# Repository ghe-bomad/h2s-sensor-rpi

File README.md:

# H2S sensor board for Raspberry Pi

An open hardware board that measures hydrogen sulphide (H2S) from 0 to 1000 ppm, with a Python package and command-line tool that read it on a Raspberry Pi over I2C. It was built for biogas monitoring and works anywhere a Raspberry Pi needs a calibrated H2S reading.

## Features

- **Sensor:** Euro-Gas 4-H2S-1000 electrochemical cell (Honeywell CLE-0113-400), 0 to 1000 ppm, overload 2000 ppm.
- **Analog front end:** TI LMP91002 potentiostat with an external 2.5 V reference (ADR3425), so the zero point does not move with the supply.
- **ADC:** 16-bit ADS1115, about 0.2 ppm per step.
- **Temperature compensation:** an NTC thermistor sits under the cell and feeds the datasheet's temperature curves, or your own.
- **Wiring:** four wires to the Pi (5 V, GND, SDA, SCL) on a screw terminal.
- **Software:** a Python package (`h2s-reader`) with calibration files, CSV logging and averaging. Its tests run without hardware.

| | |
|---|---|
| Board size | 59.7 × 31.9 mm, four M3 holes (51.5 × 23.4 mm) |
| Supply | 5 V from the Raspberry Pi, 3.3 V regulated on board |
| I2C addresses | 0x48 (LMP91002), 0x49 (ADS1115) |
| Spare input | AIN3 of the ADS1115 on a 3-pin header (GND, 3.3 V, AIN3) |

## Quick start

1. **Build or order the board** with the files in [`hardware/`](hardware/README.md), and plug the 4-H2S-1000 cell into its sockets.
2. **Wire it to the Pi:**

   | Board (CN1) | Raspberry Pi header |
   |---|---|
   | 5V | pin 2 (5 V) |
   | GND | pin 6 (GND) |
   | SDA | pin 3 (GPIO 2, SDA) |
   | SCL | pin 5 (GPIO 3, SCL) |

3. **Enable I2C and install the package:**

   ```bash
   sudo raspi-config nonint do_i2c 0
   sudo apt install -y i2c-tools python3-venv
   i2cdetect -y 1                       # shows 48 and 49
   python3 -m venv ~/h2s && ~/h2s/bin/pip install "git+https://github.com/ghe-bomad/h2s-sensor-rpi#subdirectory=software"
   ~/h2s/bin/h2s-reader --selftest
   ~/h2s/bin/h2s-reader --stream
   ```

4. **Bring the board up** as described in [docs/bring-up.md](docs/bring-up.md).
5. **Calibrate the cell** with certified test gas ([docs/calibration.md](docs/calibration.md)). Until then readings can be up to ±44 % off, because cells differ that much.

## Documentation

| | |
|---|---|
| [hardware/README.md](hardware/README.md) | schematic, bill of materials, ordering, assembly, design checks |
| [software/README.md](software/README.md) | installing, command line, Python API, calibration file, tests |
| [docs/how-it-works.md](docs/how-it-works.md) | signal chain, range and resolution, temperature compensation |
| [docs/bring-up.md](docs/bring-up.md) | first power-up and checks, notes for use in biogas |
| [docs/calibration.md](docs/calibration.md) | zero, span and temperature calibration |
| [CHANGELOG.md](CHANGELOG.md) | changes per version |

## Repository layout

```
hardware/
  kicad/            KiCad 10 project and footprints
  production/       gerbers, BOM and positions for JLCPCB (H2S-RPi-V1)
  datasheets/       cell, LMP91002 and ADS1115 datasheets
  images/           board renders
  schematic.pdf     schematic export
  check.sh          ERC, DRC and exports with kicad-cli
software/
  h2s_reader/       Python package
  tests/            pytest suite (simulated I2C bus)
  calibration.example.toml
docs/               how it works, bring-up, calibration
```

## Status

- **Version:** 1 (H2S-RPi-V1).
- **Board design:** KiCad's ERC and DRC report only reviewed, non-critical items (see [hardware/README.md](hardware/README.md#design-checks)).
- **Software:** tested against a simulated I2C bus.
- **Not yet validated:** the response to certified H2S test gas. Calibration values are still to be measured.

## License

- **Hardware** (`hardware/`): [CERN-OHL-P-2.0](LICENSE-HARDWARE).
- **Software and documentation:** [MIT](LICENSE-SOFTWARE).
- **Datasheets:** belong to their manufacturers. See [LICENSE](LICENSE).

Developed at ETH Zurich, Global Health Engineering.

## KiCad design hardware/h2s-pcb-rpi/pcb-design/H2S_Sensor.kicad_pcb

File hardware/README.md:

# Hardware

KiCad 10 project of the H2S sensor board, version H2S-RPi-V1. The full schematic is in [schematic.pdf](schematic.pdf).

| Top | Bottom |
|---|---|
|  |  |

## Circuit

| Ref | Part | Function |
|---|---|---|
| J5 | Euro-Gas 4-H2S-1000 cell (not in the BOM, order separately) | working (WE), counter (CE) and reference (RE) electrodes |
| U2 | LMP91002SDX | potentiostat: holds RE at the zero bias, converts the WE current to a voltage (7 kΩ internal gain) |
| U3 | ADR3425 | 2.5 V reference for the LMP91002 (`VREF`) |
| U7 | ADS1115IDGS | 16-bit ADC: AIN0 = LMP91002 output, AIN1 = GND, AIN2 = NTC divider, AIN3 = header H5 |
| TH1, R3 | NTC 10 kΩ (B 3950), 10 kΩ | temperature divider: 3.3 V, R3, AIN2, TH1, GND. TH1 sits under the cell |
| U1 | LP5907MFX-3.3 | 3.3 V regulator from the 5 V input |
| R1, R2 | 4.7 kΩ | I2C pull-ups to 3.3 V |
| E1 to E3 | RLSD32A051LC | bidirectional ESD protection on 5 V, SDA and SCL |
| CN1 | PA001-4P, 5.08 mm screw terminal | 5V, GND, SDA, SCL |
| H5 | 3-pin 2.54 mm header (not populated) | GND, 3.3V, AIN3 |

The LMP91002 enable pin (MENB) is tied to GND, so the chip is always on. The ADS1115 ADDR pin is tied to 3.3 V, which gives address 0x49. The LMP91002 has the fixed address 0x48.

## Connections

| CN1 | Signal | Raspberry Pi |
|---|---|---|
| 1 | 5V | pin 2 or 4 |
| 2 | GND | pin 6 |
| 3 | SDA | pin 3 (GPIO 2) |
| 4 | SCL | pin 5 (GPIO 3) |

The I2C lines are pulled up to 3.3 V on the board, which matches the Pi's logic level. Keep the cable short (under about 1 m at the default 100 kHz).

## Mechanical

- **Board:** 59.7 × 31.9 mm, 2 layers.
- **Mounting:** four M3 holes (3.2 mm), centres 51.5 × 23.4 mm apart.
- **Cell:** the 4-series cell is 20.2 mm in diameter and about 21 mm tall including its pins. The sensing face points away from the board.

## Bill of materials

The board can be assembled by JLCPCB with the files in [production/](production/). The LCSC numbers are in the BOM.

| Designator | Value | Package | LCSC |
|---|---|---|---|
| C1, C2, C6 | 1 µF | 0603 | C1592 |
| C3, C4, C5, C7 | 100 nF | 0402 | C1525 |
| CN1 | PA001-4P | 5.08 mm terminal | C173286 |
| E1, E2, E3 | RLSD32A051LC | SOD-323 | C20884 |
| R1, R2 | 4.7 kΩ | 0603 | C844460 |
| R3 | 10 kΩ | 0402 | C49330108 |
| TH1 | NTC 10 kΩ B3950 | 0603 | C7462093 |
| U1 | LP5907MFX-3.3 | SOT-23-5 | C23380874 |
| U2 | LMP91002SDX/NOPB | WSON-14 | C2651581 |
| U3 | ADR3425ARJZ-R7 | SOT-23-6 | C60864 |
| U7 | ADS1115IDGS | TSSOP-10 | C468683 |

Not in the BOM:

- **Cell:** Euro-Gas 4-H2S-1000, part number 2112B0113400. Datasheet in [datasheets/4-H2S-1000.pdf](datasheets/4-H2S-1000.pdf), shop link in [datasheets/sensor_url.txt](datasheets/sensor_url.txt).
- **Sockets for the cell's three pins:** pins are 1.5 mm in diameter; the board holes are 2.6 mm, sized for press-fit pin receptacles. The datasheet advises against soldering the cell or gluing it, because that voids the warranty and can damage it.
- **H5 header:** optional, only if you use AIN3.

## Ordering and assembly

1. **Upload** `production/H2S-RPi-V1.zip` (gerbers and drill files) to JLCPCB. Choose 2 layers and 1.6 mm thickness.
2. **For assembly,** add `H2S-RPi-V1_bom.csv` and `H2S-RPi-V1_positions.csv`. Check the part rotations in the assembly preview, especially U2, U3 and U7.
3. **Fit the cell sockets** by hand, then plug in the cell. The cell's WE pin is the one on its own, matching the footprint's pad 1.
4. **To regenerate the production files after a change,** use the KiCad plugin "Fabrication Toolkit" (settings in `kicad/fabrication-toolkit-options.json`). It writes to `kicad/production/`; move the files to `production/`.

## Editing the design

- **Symbols:** the schematic embeds them, so it opens on any KiCad 10 installation.
- **Footprints:** most come from LCSC via [easyeda2kicad](https://github.com/uPesy/easyeda2kicad.py). The two custom ones (cell, WSON-14) are in `kicad/H2S_Sensor.pretty`.
- **3D models:** they refer to `${EASYEDA2KICAD}`. Without that library the 3D view and the renders show the bare pads of those parts.

## Design checks

Run `hardware/check.sh` (needs `kicad-cli` from KiCad 10). It writes ERC and DRC reports to `hardware/reports/` and regenerates `schematic.pdf` and the renders. The current findings are reviewed and none of them needs a change:

| Check | Finding | Assessment |
|---|---|---|
| ERC | pins of type "Unspecified" connected to other pins (40) | symbols imported with easyeda2kicad have no pin types. Cosmetic |
| ERC | power input pins not driven (C1, C6) | no PWR_FLAG symbols on the 3.3 V and VREF nets. Cosmetic |
| ERC | input pin not driven: E3 pin 2, U7 AIN3 | E3 is an ESD diode; AIN3 goes to the optional header H5 |
| ERC | GND and MENB on the same net | intended: MENB is tied to GND |
| ERC | one unconnected wire end | a short leftover wire stub, no electrical effect |
| DRC | courtyards of TH1 and J5 overlap | intended: the NTC sits under the cell |
| DRC | silkscreen clipped by the solder mask at J5 | cosmetic |
| DRC | 4 pads of U2 without a schematic pin | the vias in the WSON-14 thermal pad, all GND |
| DRC | H5 "do not populate" differs between symbol and footprint | H5 is optional |
| DRC | missing field ALTIUM_VALUE (25) | leftover from the easyeda2kicad import |

## Ideas for a next revision

- **Filter capacitor:** add a footprint between the LMP91002 pins C1 and C2 (now unconnected) for hardware low-pass filtering of the amplifier output.
- **Power flags:** add PWR_FLAG symbols and pin types so ERC runs clean.
- **Test points:** add them for 3.3 V, VREF and the amplifier output.

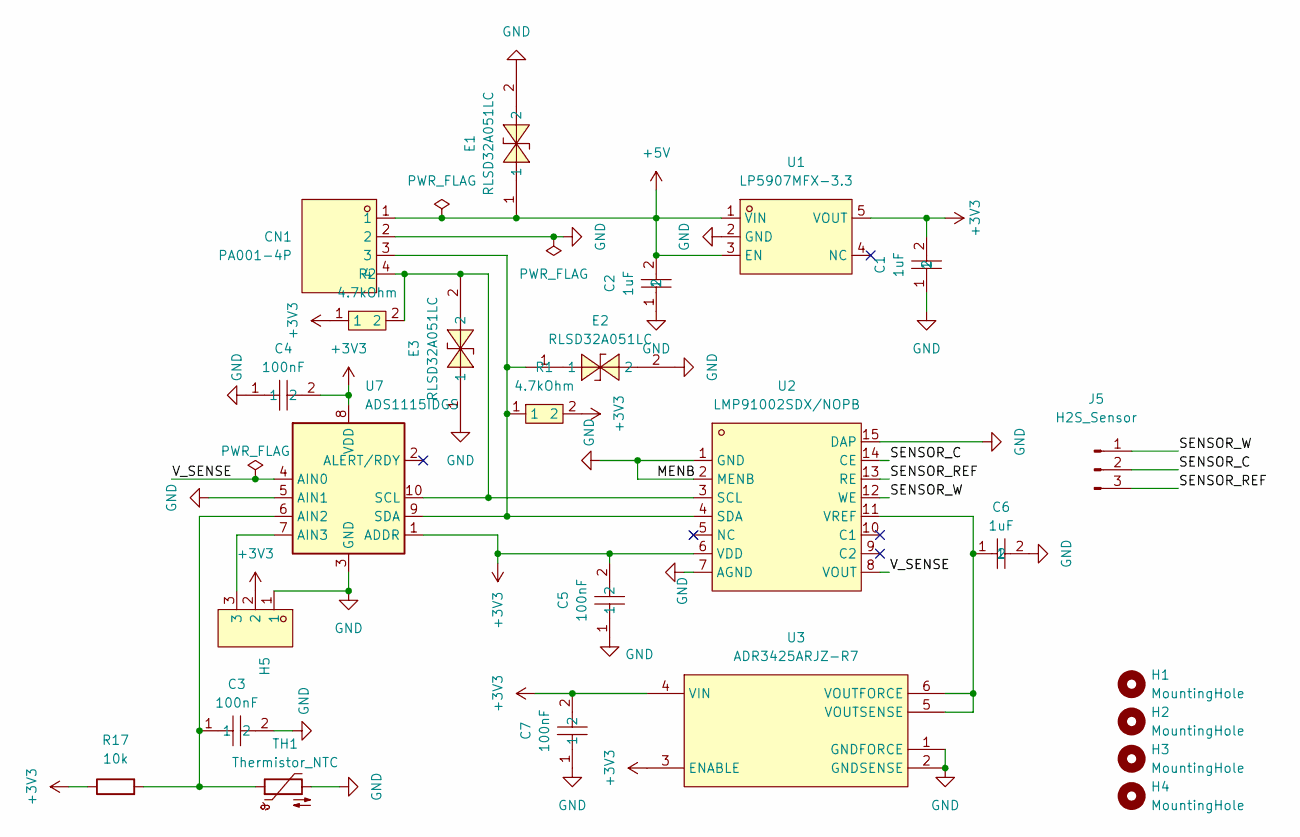
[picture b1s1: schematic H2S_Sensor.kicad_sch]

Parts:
C1, C2, C6: 1uF; C0603; MPN CL10A105KO8NNNC; LCSC Part C1592
C3, C4, C5, C7: 100nF; C0402; LCSC Part C1525
CN1: PA001-4P; CONN-TH_4P-P5.08_PA001-4P; MPN PA001-4P; LCSC Part C173286
E1, E2, E3: RLSD32A051LC; SOD-323_L1.8-W1.3-LS2.5-BI; MPN RLSD32A051LC; LCSC Part C20884
H1, H2, H3, H4: MountingHole; MountingHole_3.2mm_M3
H5: HX PH254-01-03-Z-L11.5 PCB PIN HEADER; HDR-TH_3P-P2.54-V-M-1; MPN HX PH254-01-03-Z-L11.5 pcb pin header; LCSC Part C52016391
J5: H2S_Sensor; H2S_Sensor_3Pin_D20mm
R1, R2: 4.7kOhm; R0603; MPN TNPW06034K70BEEA; LCSC Part C844460
R17: 10k; R_0603_1608Metric; LCSC Part C25804
TH1: Thermistor_NTC; R_0603_1608Metric; LCSC Part C7462093
U1: LP5907MFX-3.3; SOT-23-5_L3.0-W1.7-P0.95-LS2.8-BR; MPN LP5907MFX-3.3; LCSC Part C23380874
U2: LMP91002SDX/NOPB; WSON-14_L4.0-W4.0-P0.50-BL-EP; MPN LMP91002SDX/NOPB; LCSC Part C2651581
U3: ADR3425ARJZ-R7; SOT-23-6_L2.9-W1.6-P0.95-LS2.8-BR; MPN ADR3425ARJZ-R7; LCSC Part C60864
U7: ADS1115IDGS; TSSOP-10_3x3mm_P0.5mm; LCSC Part C468683

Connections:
+3V3: C1.2, C4.2, C5.2, C7.2, H5.2, R1.2, R2.1, R17.1, U1.5 (VOUT), U2.6 (VDD), U3.3 (ENABLE), U3.4 (VIN), U7.1 (ADDR), U7.8 (VDD); also elsewhere on the board
+5V: C2.2, CN1.1, E1.1, U1.1 (VIN), U1.3 (EN)
/SENSOR_C: J5.2, U2.14 (CE)
/SENSOR_REF: J5.3, U2.13 (RE)
/SENSOR_W: J5.1, U2.12 (WE)
/V_SENSE: U2.8 (VOUT), U7.4 (AIN0)
GND: C1.1, C2.1, C3.2, C4.1, C5.1, C6.2, C7.1, CN1.2, E1.2, E2.2, E3.1, H5.1, TH1.2, U1.2 (GND), U2.1 (GND), U2.2 (MENB), U2.7 (AGND), U2.15 (DAP), U3.1 (GNDFORCE), U3.2 (GNDSENSE), U7.3 (GND), U7.5 (AIN1)
unnamed: CN1.4, E3.2, R2.2, U2.3 (SCL), U7.10 (SCL)
unnamed: CN1.3, E2.1, R1.1, U2.4 (SDA), U7.9 (SDA)
unnamed: C6.1, U2.11 (VREF), U3.5 (VOUTSENSE), U3.6 (VOUTFORCE)
unnamed 10: C3.1, R17.2, TH1.1, U7.6 (AIN2); also elsewhere on the board
unnamed: H5.3, U7.7 (AIN3)

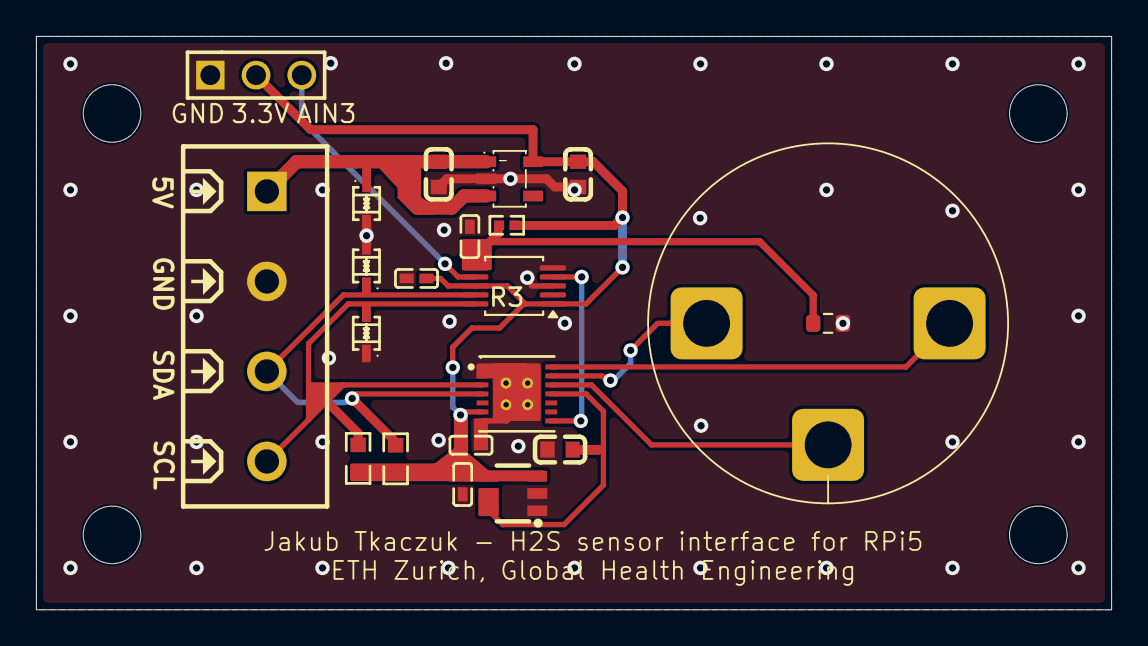
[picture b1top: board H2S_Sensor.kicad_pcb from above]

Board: 2 copper layers, 59.7 x 31.8 mm, 25 parts (0 on the bottom side), 12 nets.

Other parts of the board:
R3: 10k; R0402

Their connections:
+3V3: R3.1; also elsewhere on the board
unnamed 10: R3.2; also elsewhere on the board
